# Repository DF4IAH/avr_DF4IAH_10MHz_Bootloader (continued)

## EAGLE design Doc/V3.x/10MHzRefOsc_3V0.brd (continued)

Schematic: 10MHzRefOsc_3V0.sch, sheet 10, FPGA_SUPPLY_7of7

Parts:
C1001: 100uF; C1206
C1002, C1003, C1022, C1023: 4.7uF; C0402
C1004, C1005, C1006, C1012, C1024, C1025, C1026: 0.47uF; C0402
C1011, C1021: 47uF; C0805
R101, R102, R103, R104, R105: 0; R0402
U1: XC7A35TFTG256; FTG256_0MM4

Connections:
FPGA_DXN_0: R105.1, U1.K7 (DXN_0)
FPGA_DXP_0: R104.1, U1.K8 (DXP_0)
FPGA_VCCAUX: C1021.1, C1022.1, C1023.1, C1024.1, C1025.1, C1026.1, R103.1, U1.G10 (VCCAUX), U1.J10 (VCCAUX), U1.K11 (VCCAUX), U1.L10 (VCCAUX)
FPGA_VCCBRAM: C1011.1, C1012.1, R102.1, U1.E10 (VCCBRAM), U1.F11 (VCCBRAM)
FPGA_VCCINT: C1001.1, C1002.1, C1003.1, C1004.1, C1005.1, C1006.1, R101.1, U1.F7 (VCCINT), U1.F9 (VCCINT), U1.G6 (VCCINT), U1.H9 (VCCINT), U1.J6 (VCCINT), U1.K9 (VCCINT), U1.L8 (VCCINT)
GND: C1001.2, C1002.2, C1003.2, C1004.2, C1005.2, C1006.2, C1011.2, C1012.2, C1021.2, C1022.2, C1023.2, C1024.2, C1025.2, C1026.2, R104.2, R105.2, U1.A1 (GND), U1.A11 (GND), U1.B8 (GND), U1.C5 (GND), U1.C15 (GND), U1.D2 (GND), U1.D12 (GND), U1.E9 (GND), U1.F6 (GND), U1.F10 (GND), U1.F16 (GND), U1.G3 (GND), U1.G9 (GND), U1.G13 (GND), U1.H6 (GND), U1.J9 (GND), U1.J11 (GND), U1.K4 (GND), U1.K6 (GND), U1.K14 (GND), U1.L1 (GND), U1.L11 (GND), U1.M8 (GND), U1.N5 (GND), U1.N15 (GND), U1.P2 (GND), U1.P12 (GND), U1.R9 (GND), U1.T6 (GND), U1.T16 (GND); also elsewhere on the board
PWR_1V0: R101.2, R102.2
PWR_1V8: R103.2; also elsewhere on the board

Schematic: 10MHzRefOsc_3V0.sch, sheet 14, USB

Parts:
C141: 47uF; PANASONIC_C
C142: 100n; C0805
CON141: TYCO-AMP_USBUSB-B_SMT; TYCO-AMP_USB-B_SMT
D141, D142: BZX84-C3V6; TO236
R141, R142: 68; R0805
R143: 1M; R0805
R144: 1.5k; R0805
RP141: 1206L025YR_0.5A; M1206

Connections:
GND: C141.-, C142.2, CON141.4 (GND), D141.A, D142.A, R143.1; also elsewhere on the board
USB_5V: C141.+, C142.1, RP141.2
USB_DISC: R144.2
USB_D_MIN1: CON141.2 (D-), D142.C, R142.1, R144.1
USB_D_MNS: R142.2
USB_D_PLS: R141.2
USB_D_PLS1: CON141.3 (D+), D141.C, R141.1, R143.2
USB_PWR1: CON141.1 (VBUS), RP141.1

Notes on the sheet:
USB-B

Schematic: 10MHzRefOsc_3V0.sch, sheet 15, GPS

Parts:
C151: 0.22F; PANASONIC_C
C152: 100n; C0805
CON151: HEADER-2X5SMD; 2X5SMD
D151: CRS08; SOT23
R151, R152: 10k; R0805
RP151: 1206L012WR_0.1A; M1206
U151: GLOBALTOP-FIREFLY1-GMM-G3

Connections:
GND: C151.-, C152.2, CON151.1, CON151.9, CON151.10, U151.2 (GND), U151.4 (GND), U151.8 (GND), U151.10 (GND), U151.15 (GND); also elsewhere on the board
GPS_2ND_RX: R152.1, U151.6 (RXDB)
GPS_2ND_TX: U151.5 (TXDB)
GPS_3DFIX: U151.13 (3D_FIX)
GPS_ANT: U151.1 (ANTENNA_IN); also elsewhere on the board
GPS_ANT_PWR: CON151.4, RP151.1, U151.3 (VANT)
GPS_NMEA_RX: CON151.5, U151.12 (RXDA)
GPS_NMEA_TX: CON151.6, U151.11 (TXDA)
GPS_NRESET: R151.1, U151.7 (NRESET)
GPS_PPS: CON151.7, U151.9 (1PPS)
PWR_3V3: C152.1, D151.1 (A), R151.2, R152.2, RP151.2, U151.16 (VCC_3V3); also elsewhere on the board
PWR_5V0: CON151.3
PWR_BACKUP_GPS: C151.+, CON151.2, D151.3 (C), U151.14 (VBACKUP)

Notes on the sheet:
GPS - PINs: 1 GND 2 V_BAT, Memory Supply, Goldcap 3 VCC 5V 4 V_ANT 5V, fused 5 GPS NMEA RX 6 GPS NMEA TX 7 PPS (1 Hz) 8 Ref. 10 kHz 9 GND 10 GND

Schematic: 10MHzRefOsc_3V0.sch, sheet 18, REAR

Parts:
CON181, CON183, CON184, CON185, CON186: MCX-J-P-X-RA-SM1
CON182: SD-73100-0105; MOLEX_BNC-JACK-50R_SD-73100-0105

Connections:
GND: CON181.2, CON181.3, CON181.4, CON181.5, CON182.2, CON182.3, CON183.2, CON183.3, CON183.4, CON183.5, CON184.2, CON184.3, CON184.4, CON184.5, CON185.2, CON185.3, CON185.4, CON185.5, CON186.2, CON186.3, CON186.4, CON186.5; also elsewhere on the board
GPS_ANT: CON181.1; also elsewhere on the board
REFC_10MHZ: CON182.1
SIG_CH0_I: CON183.1
SIG_CH0_Q: CON184.1
SIG_CH1_I: CON185.1
SIG_CH1_Q: CON186.1

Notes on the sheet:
10 MHz RefClk Out
GPS Ant In
CH0 I Out
CH0 Q Out
CH1 I Out
CH1 Q Out

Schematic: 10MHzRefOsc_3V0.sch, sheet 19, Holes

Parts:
H191, H192, H193, H194: MOUNT-PAD-ROUND2.8; 2,8-PAD

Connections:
GND: H191.B2,8, H192.B2,8, H193.B2,8, H194.B2,8; also elsewhere on the board

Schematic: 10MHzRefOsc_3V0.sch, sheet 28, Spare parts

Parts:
CON191: HEADER-2X3SMD; 2X03SMD
CON192: AVR-JTAG-10SMD; 2X5SMD
D191: BZX84-C2V7; TO236
L191: 10uH; L1812

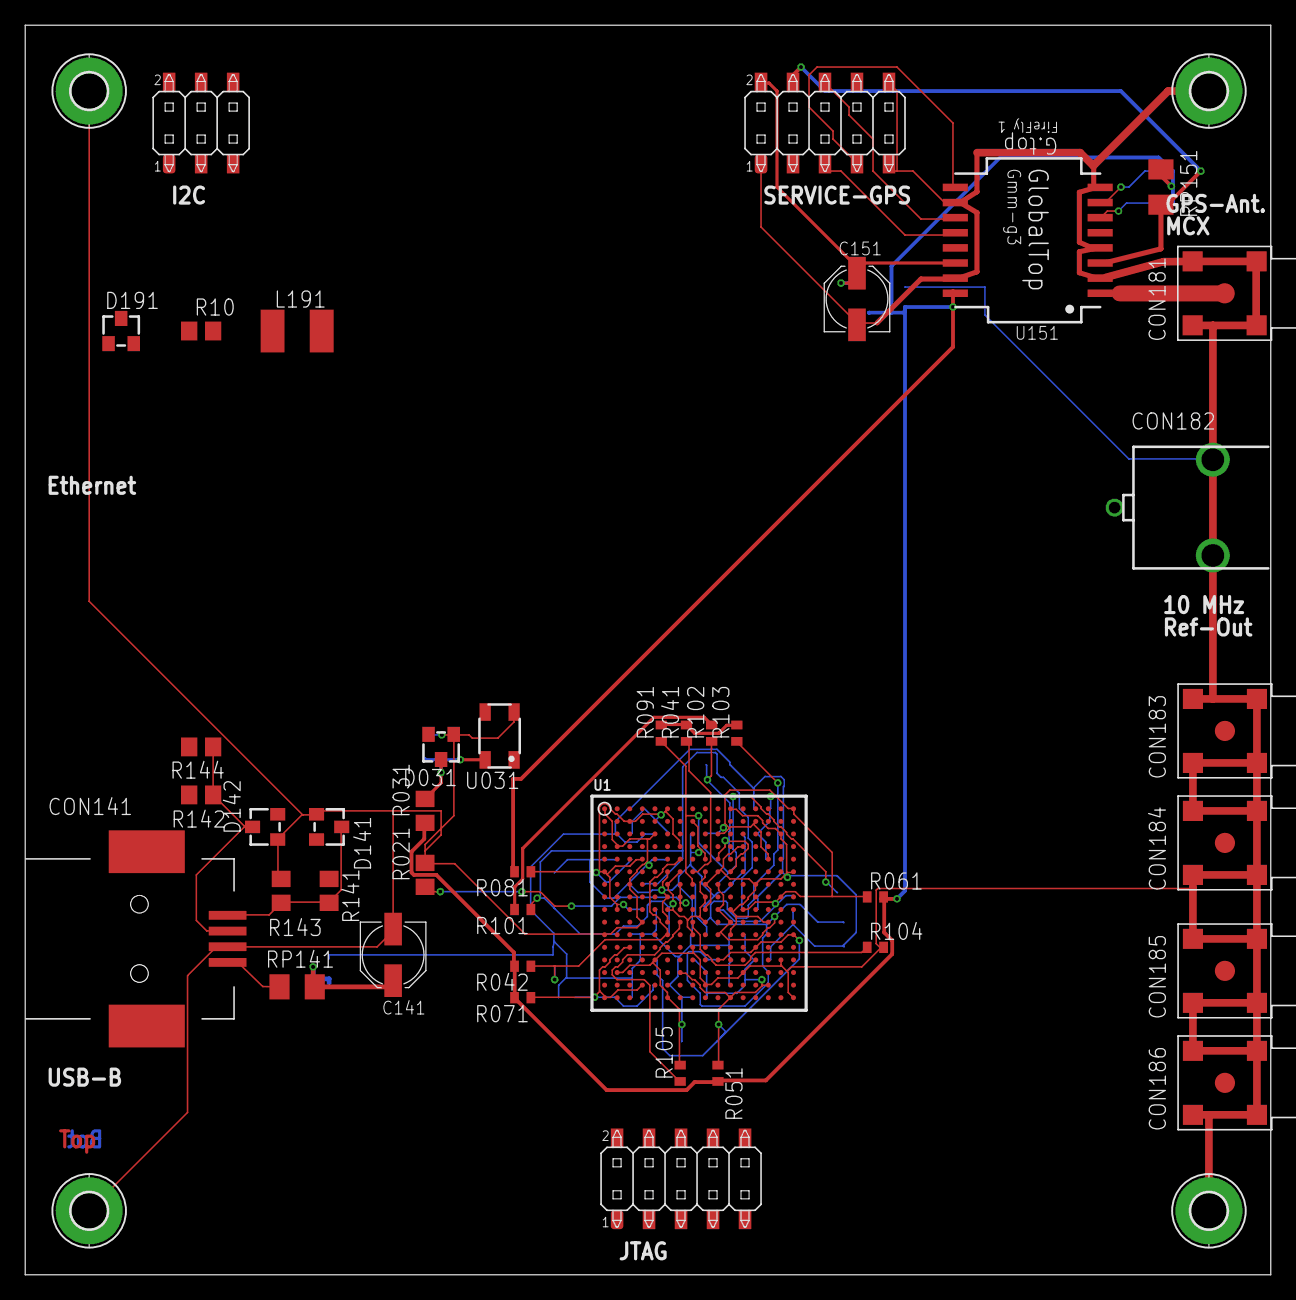
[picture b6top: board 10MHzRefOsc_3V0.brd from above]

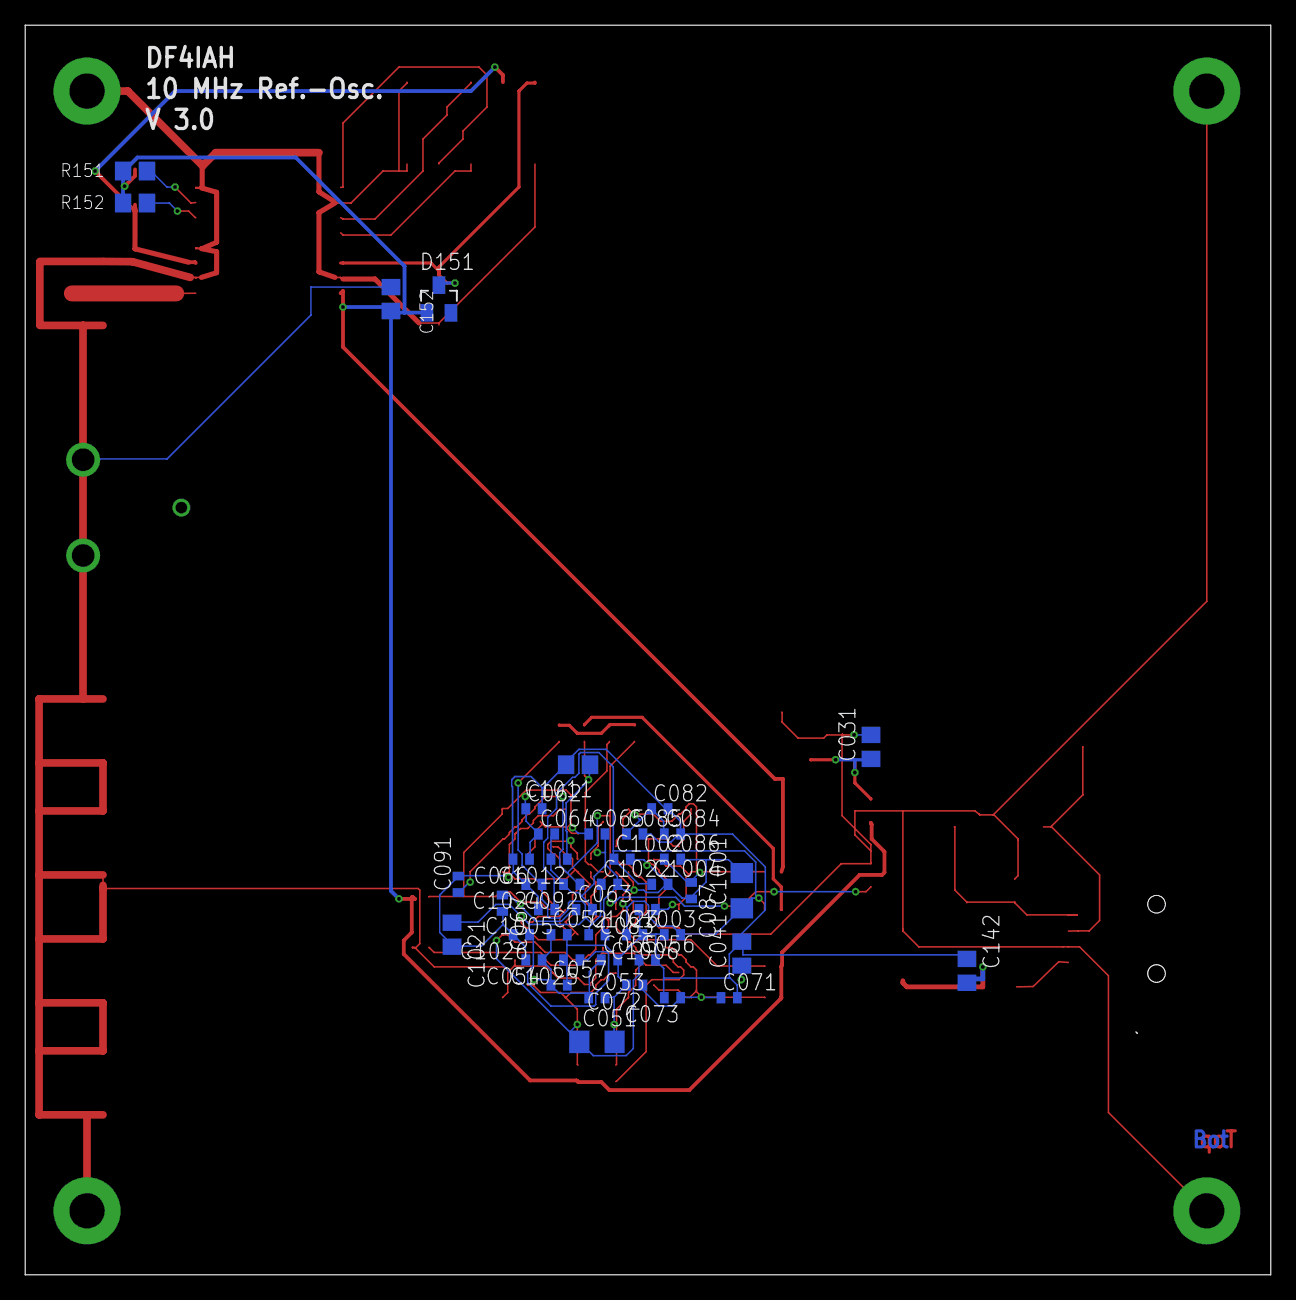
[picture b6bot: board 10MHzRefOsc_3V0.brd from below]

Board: 2 copper layers, 98.9 x 99.2 mm, 90 parts (45 on the bottom side), 30 nets.

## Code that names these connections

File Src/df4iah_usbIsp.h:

/*
 * isp.h - part of USBasp
 *
 * Autor..........: Thomas Fischl <tfischl@gmx.de>
 * Description....: Provides functions for communication/programming
 *                  over ISP interface
 * Licence........: GNU GPL v2 (see Readme.txt)
 * Creation Date..: 2005-02-23
 * Last change....: 2009-02-28
 */

#ifndef DF4IAH_USBISP_H_
#define	DF4IAH_USBISP_H_

#ifndef uchar
#define	uchar	unsigned char
#endif

#define	ISP_OUT   PORTB
#define ISP_IN    PINB
#define ISP_DDR   DDRB
#define ISP_RST   PB2
#define ISP_MOSI  PB3
#define ISP_MISO  PB4
#define ISP_SCK   PB5

/* Prepare connection to target device */
void ispConnect();

/* Close connection to target device */
void ispDisconnect();

/* read an write a byte from ISP using software (slow) */
uchar ispTransmit_sw(uchar send_byte);

/* read an write a byte from ISP using hardware (fast) */
uchar ispTransmit_hw(uchar send_byte);

/* enter programming mode */
uchar ispEnterProgrammingMode();

/* read byte from EEPROM at given address */
uchar ispReadEEPROM(unsigned int address);

/* write byte to Flash at given address */
uchar ispWriteFlash(unsigned long address, uchar data, uchar pollmode);

uchar ispFlushPage(unsigned long address, uchar pollvalue);

/* read byte from Flash at given address */
uchar ispReadFlash(unsigned long address);

/* write byte to EEPROM at given address */
uchar ispWriteEEPROM(unsigned int address, uchar data);

/* pointer to SW or HW transmit function */
uchar (*ispTransmit)(uchar);

/* set SCK speed. call before ispConnect! */
void ispSetSCKOption(uchar sckoption);

/* load extended address byte */
void ispLoadExtendedAddressByte(unsigned long address);

#endif /* DF4IAH_USBISP_H_ */

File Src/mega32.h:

#ifndef _MEGA32_H_
#define _MEGA32_H_

/* Part-Code ISP */
#define DEVTYPE_ISP     	0x72
/* Part-Code Boot */
#define DEVTYPE_BOOT    	0x73

#define SIG_BYTE1			0x1E
#define SIG_BYTE2			0x95
#define SIG_BYTE3			0x02

/* USART */
#define UART_BAUD_HIGH		UBRR0H
#define UART_BAUD_LOW		UBRR0L
#define UART_STATUS			UCSR0A
#define UART_TXREADY		UDRE0
#define UART_RXREADY		RXC0
#define UART_DOUBLE			U2X0
#define UART_CTRL			UCSR0B
#define UART_CTRL_DATA		(_BV(TXEN0 | _BV(RXEN0))	// TX enable, RX enable
#define UART_CTRL2			UCSR0C
#define UART_CTRL2_DATA		(0b11 << UCSZ00)			// 8-bit
#define UART_DATA			UDR0
#define UART_PORT			PORTD						// port D register
#define UART_DDR			DDRD						// DDR for port D
#define UART_TX_PIN			PIND						// PIN for TX pin at port D
#define UART_TX_PNUM		PIN1						// PIN number for TX pin
#define UART_RX_PIN			PIND						// PIN for RX pin at port D
#define UART_RX_PNUM		PIN0						// PIN number for RX pin

/* Timer-n compare output */
#define DDR_OC0A_REG		DDRD
#define DDR_OC0A			PD6
#define DDR_OC0B_REG		DDRD
#define DDR_OC0B			PD5
#define DDR_OC1A_REG		DDRB
#define DDR_OC1A			PB1
#define DDR_OC1B_REG		DDRB
#define DDR_OC1B			PB2
#define DDR_OC2A_REG		DDRB
#define DDR_OC2A			PB3
#define DDR_OC2B_REG		DDRD
#define DDR_OC2B			PD3

/*
 * Pin "STARTPIN" on port "STARTPORT" in this port has to grounded
 * (active low) to start the bootloader
 */
#define PROBE_DDR			DDRD
#define PROBE_PORT			PORTD
#define PROBE_PIN			PIND
#define PROBE_PNUM			PIN3						// JP3 BootLoader

/* Debugging toggle pin */
#define PWMTOGGLEPIN_DDR	DDRC
#define PWMTOGGLEPIN_PORT	PORTC
#define PWMTOGGLEPIN_PIN	PINC
#define PWMTOGGLEPIN_PNUM	PIN5						// PC5(ADC5/SCL) - Pin 28

/* BOOT token and place of BOOT token as offset before RAMEND */
# define BOOT_TOKEN			0xb00f
# define BOOT_TOKEN_EE_ADR	0x3fa						// @see df4iah_fw_memory.h

#endif // #ifndef _MEGA32_H_

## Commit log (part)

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2014-10-25 avr_DF4IAH_Bootloader - copy from avr_Bootloader_0v85
2014-10-25 avr_DF4IAH_Bootloader - first compilation
2014-10-25 avr_DF4IAH_Bootloader - Src subdirectory established
2014-10-30 avr_DF4IAH_Bootloader - changed bootsize to 2k-words, starting @ 0x7000
2014-11-01 avr_DF4IAH_Bootloader - compatibility with AVR109 established, compared with Bootloader of HF-Messzwerg
2014-11-02 avr_DF4IAH_Bootloader - some more refactoring
2014-11-02 avr_DF4IAH_Bootloader - some more tweaks done for usbdrv setup
2014-11-02 avr_DF4IAH_Bootloader - code placement added
2014-11-02 avr_DF4IAH_Bootloader - between serial and usb can now be selected
2014-11-24 avr_DF4IAH_Bootloader - between serial and usb can now be selected (2)
2014-11-27 avr_DF4IAH_Bootloader - PWM output to pull crystal added (2)
2014-11-27 avr_DF4IAH_Bootloader - fire-up the first time (2)
2014-11-27 avr_DF4IAH_Bootloader - fire-up the first time (3)
2014-11-27 avr_DF4IAH_Bootloader - wireDebug disabled
2014-11-27 avr_DF4IAH_Bootloader - BrownOutDetection=2.7V, DebugWire=on, ISP=on
2014-11-27 avr_DF4IAH_Bootloader - moved debug_endlessTogglePin() before init_usb()
2014-11-27 avr_DF4IAH_Bootloader - USB_CFG_HAVE_MEASURE_FRAME_LENGTH disabled
2014-11-28 avr_DF4IAH_Bootloader - USB device description changed to USBasp (2)
2014-11-28 avr_DF4IAH_Bootloader - USBasp firmware included
2014-11-28 avr_DF4IAH_Bootloader - USBasp stack joined with avrboot code
2014-11-29 avr_DF4IAH_Bootloader - with this configuration USB works :-)
2014-11-29 avr_DF4IAH_Bootloader - with this configuration USB still works :-)
2014-11-30 avr_DF4IAH_Bootloader - wrong assumptions corrected, we do not use the Tiny Programming Interface (TPI)
2014-11-30 avr_DF4IAH_Bootloader - Release added to the ignore list
2014-11-30 avr_DF4IAH_Bootloader - mimic signature - bad response
2014-11-30 avr_DF4IAH_Bootloader - EEPROM and Flash, READ and WRITE now OK :-)
2014-11-30 avr_DF4IAH_Bootloader - enhancing Flash WRITE to automagically erasing pages during write operation
2014-11-30 avr_DF4IAH_Bootloader - new memory layout
2014-11-30 avr_DF4IAH_Bootloader - USB poll interval increased to 25 ms
2014-12-01 avr_DF4IAH_Bootloader - SPI does only work when DebugWire is turned off
2014-12-03 avr_DF4IAH_Bootloader - writeFlashPage rewritten
2014-12-03 avr_DF4IAH_Bootloader - writeFlashPage() is OK now
2014-12-03 avr_DF4IAH_Bootloader - writeFlashPage() is OK now (2)
2014-12-04 avr_DF4IAH_Bootloader - renaming done to distinguish between BL (bootloader) and FW (code) (2)
2014-12-04 avr_DF4IAH_Bootloader - bootloader and firmware distinguished
2014-12-04 avr_DF4IAH_Bootloader - bootloader and firmware distinguished (2)
2014-12-04 avr_DF4IAH_Bootloader - bad APP_END behavior in memory_bl_writeFlashPage corrected
2014-12-06 avr_DF4IAH_Bootloader - programming fuses added
2014-12-13 avr_DF4IAH_Bootloader - usbFunctionSetup() cleaned up
2014-12-24 avr_DF4IAH_Bootloader - try new swap bootloader and memory layout
2014-12-24 avr_DF4IAH_Bootloader - sample TOKEN bytes at the start-up
2014-12-24 avr_DF4IAH_Bootloader - jump to FW and BL now OK
2014-12-24 avr_DF4IAH_Bootloader - jump to FW and BL now OK (3)
2014-12-25 avr_DF4IAH_Bootloader - USB bug removed
2014-12-26 avr_DF4IAH_Bootloader - switch off modules that are not needed, USB power: 210 mA
2014-12-27 avr_DF4IAH_Bootloader - new default PWM value 0xC000
2014-12-28 avr_DF4IAH_Bootloader - version string updated
2014-12-28 avr_DF4IAH_Bootloader - redefinition of BOOT_TOKEN removed
2014-12-29 avr_DF4IAH_Bootloader - address of BOOT_TOKEN changed
2014-12-29 avr_DF4IAH_Bootloader - DEFAULT_PWM_COUNT changed to 0xB800
2014-12-29 avr_DF4IAH_Bootloader - toggle PIN not masked correctly (2)
2014-12-29 avr_DF4IAH_Bootloader - volatile reduced
2014-12-30 avr_DF4IAH_Bootloader - Hardware V1.1 --> V1.2
2014-12-31 avr_DF4IAH_Bootloader - new default startup PWM value
2014-12-31 avr_DF4IAH_Bootloader - startup PWM value up-heated oscillator
2015-01-01 avr_DF4IAH_Bootloader - startup PWM value up-heated oscillator (2)
2015-01-15 avr_DF4IAH_Bootloader - CPLD - moved here
2015-01-15 avr_DF4IAH_Bootloader - CPLD - VHDL TestBench added - TODO: functional and timing simulations
2015-01-15 avr_DF4IAH_Bootloader - Doc - Eagle: last updates of the circuit added (V2.0)
2015-01-16 avr_DF4IAH_Bootloader - CPLD - serial communication paths added
2015-01-18 avr_DF4IAH_Bootloader - Doc - Eagle: USB-B and BNC connectors changed
2015-01-18 avr_DF4IAH_Bootloader - Doc - Eagle: ISP-Connector changed from old 10 to new 6 pin variant
2015-01-20 avr_DF4IAH_Bootloader - Doc - Eagle: V2.0.1 manufactured by PCB-Pool - corrections needed
2015-01-26 avr_DF4IAH_Bootloader - Doc - Eagle: setting-up V3.0
2015-01-26 avr_DF4IAH_Bootloader - Doc - Eagle: V3.0 - REAR panel connected
2015-01-27 avr_DF4IAH_Bootloader - Doc - Eagle: current df4iah.lbr added
2015-01-27 avr_DF4IAH_Bootloader - Doc - Eagle: V2.1 after manufacturing by PCB-Pool - findings to be fixed (2) - BNC-Drills size doubled, Goldcap bigger than assumed, switching converter had wrong PIN assignme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
2015-01-28 avr_DF4IAH_Bootloader - Doc - Eagle: V3.0 - FPGA and MMU, first attempt, added
2015-02-01 avr_DF4IAH_Bootloader - Doc - Eagle: df4iah.lbr - LINX RXM-GNSS-TM chip entries corrected
2015-02-01 avr_DF4IAH_Bootloader - Doc - Eagle: V2.1 after manufacturing by PCB-Pool - findings to be fixed (4) - change R81 from 1k to 150Ohm, 3.3V regulator corrected.
2015-02-04 avr_DF4IAH_Bootloader - Doc - Eagle: V3.0 - MMU (AVR ATmega) moved into FPGA using a free MMU core from opencores.org.
2015-02-04 avr_DF4IAH_Bootloader - Doc - Eagle: V3.0 - xilinx_devices_V6.lbr containing XC7-Artix added (2)
2015-02-05 avr_DF4IAH_Bootloader - Doc - Eagle: structuring into V1.x, V2.x and V3.x (1)
2015-02-05 avr_DF4IAH_Bootloader - Doc - Eagle: structuring into V1.x, V2.x and V3.x (3)
2015-02-05 avr_DF4IAH_Bootloader - CPLD - multiple changes, now CPLD works as intended
2015-02-07 avr_DF4IAH_Bootloader - Doc - Eagle: main df4iah.lbr library split into sub-libraries
2015-02-07 avr_DF4IAH_Bootloader - Doc - Eagle: V2.1 - OP-Amps U4 and U5 added/changed
2015-02-15 avr_DF4IAH_Bootloader - Doc - Eagle: V2.1 - Sample&Hold - reduce from 10nF to 100pF, components are renamed (2)
2015-02-15 avr_DF4IAH_Bootloader - CPLD - V2.1 uses GPS PPS-signal only, switch from 10kHz to 1Hz
2015-02-16 avr_DF4IAH_Bootloader - CPLD - V2.1 uses CPLD to drive the PWM_PULL RC-network due to the regulated 3.3V source of the CPLD. The AVR is at 5.0V unregulated USB-Bus that resulted in non-accurate pull 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
2015-02-17 avr_DF4IAH_Bootloader - Doc - Compilation-SizeCompare - added. Win7 results are outdated.
2015-02-17 avr_DF4IAH_Bootloader - Doc - Copilation-SizeCompare - Bootloader/Ubuntu added
2015-02-17 avr_DF4IAH_Bootloader - Doc - Compilation-SizeCompare - MAC Bootloader/Firmware updated
2015-02-19 avr_DF4IAH_Bootloader - default PWM value modified
2015-02-19 avr_DF4IAH_Bootloader - Doc - Eagle: V2.1 - R411 modified, CPLD pinout changed
2015-02-24 avr_DF4IAH_Bootloader - Src - df4iah_bl_clkPullPwm module now without clkPullPwm_bl_setRatio(), DEFAULT_PWM_COUNT changed from 155 to 90.
2015-02-25 avr_DF4IAH_Bootloader - Src - avrdude programming e-fuse: keep D.C.s at '1'
2015-02-25 avr_DF4IAH_Bootloader - Revert most changes on mega32.h. Moved extras to df4iah_bl_main.h
2015-03-01 avr_DF4IAH_Bootloader - Src - avr-size switched from Berkeley to SYSV format. Using UTF-8 for all files now.
2015-03-01 avr_DF4IAH_Bootloader - Doc - Eagle: V2.1 - PWM pull signal via CPLD for clamping signals to defined values. AVR controller @ USB is not voltage regulated, the PWM output is therefore variable in its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
2015-03-12 avr_DF4IAH_Bootloader - CPLD - 10 MHz out signal negated to have that signal in phase with the 1PPS signal
2015-03-17 avr_DF4IAH_Bootloader - Doc - Eagle: V2.1 - with GPS module Linx - sent to DirtyPCBs
2015-03-17 avr_DF4IAH_Bootloader - Doc - Eagle: V2.2 - with GPS module GlobalTop - sent to DirtyPCBs
2015-03-26 avr_DF4IAH_Bootloader - Doc - Eagle: V2.2 - correction: CRS80 --> CRS08
2015-03-26 avr_DF4IAH_Bootloader - Doc - Eagle: V2.1 - correction: CRS80 --> CRS08 (2)
2015-03-26 avr_DF4IAH_Bootloader - Doc - Eagle: V2.x - *.pro files removed
2015-03-30 avr_DF4IAH_Bootloader - Doc - Eagle: V2.1/V2.2 - removed elkos and replaced it by C0805 MLCCs
2015-04-09 avr_DF4IAH_Bootloader - CPLD - simple PWM transfer added: 5V in, 3.3V out
2015-04-12 avr_DF4IAH_Bootloader - Doc - Eagle: V2.3 - added. Contains GPS-module TJ1513MTBD which is based on the MediaTek MT3333 chip-set (2)
2015-04-20 avr_DF4IAH_Bootloader - Doc - Eagle: 2.x - 10 MHz signal spectrum
2015-04-20 avr_DF4IAH_Bootloader - Doc - Versandtaschen added (2)
2015-04-20 avr_DF4IAH_Bootloader - Doc - Eagle: 2.1, 2.2, 2.3 - three resistors changed
2015-04-23 avr_DF4IAH_Bootloader - Doc - Versandtasche for LCD-Module updated
2015-04-24 avr_DF4IAH_Bootloader - Doc - naming of 10MHz-Ref-Osc corrected (1)
2015-04-24 avr_DF4IAH_Bootloader - Doc - Versandtasche for 10MHzRefOsc updated
2015-04-24 avr_DF4IAH_Bootloader - Doc - Versandtasche for 10MHzRefOsc updated - R311 correction (2)
2015-04-25 avr_DF4IAH_Bootloader - CPLD - variant: 1 MHz instead of 10 MHz output
2015-04-25 avr_DF4IAH_Bootloader - Doc - Versandtasche for 10MHzRefOsc updated - CPLD: current RTL images included
2015-04-25 avr_DF4IAH_Bootloader - CPLD - now 10 MHz (default) or 1 MHz (low @ 10 kHz input line) at BNC (Pin 40)
2015-04-25 avr_DF4IAH_Bootloader - Doc - Versandtasche for 10MHzRefOsc updated - CPLD: 10/1 MHz select, RTL pictures updated
2015-04-25 avr_DF4IAH_Bootloader - Doc - Versandtasche for 10MHzRefOsc updated - CPLD: 10/1 MHz select, RTL pictures updated (2)
2015-04-29 avr_DF4IAH_Bootloader - CPLD - 2.5 MHz sync'ing 0° and 180° to be ready in less time
2015-04-29 avr_DF4IAH_Bootloader - CPLD - invertion of 10 MHz removed
2015-05-08 avr_DF4IAH_Bootloader - Doc - Eagle: 2.2 - 3.3V adjusting resistors corrected
2015-05-11 avr_DF4IAH_Bootloader - Doc - ISP - ISP__avr_DF4IAH_Bootloader.hex 20150312 added
2015-05-11 avr_DF4IAH_Bootloader - Doc - ISP - ISP__avr_DF4IAH_10MHz_Reference.hex, ISP__avr_DF4IAH_10MHz_Reference.eep 20150429 added
2015-05-11 avr_DF4IAH_Bootloader - Doc - ISP - ISP programming scripts added (2)
2015-05-11 avr_DF4IAH_Bootloader - CPLD - df4iah_10mhz_ref_osc_v2.lct removed
2015-05-11 avr_DF4IAH_Bootloader - CPLD - df4iah_10mhz_ref_osc_v2.svf updated (2)
2015-05-12 avr_DF4IAH_Bootloader - CPLD - df4iah_10mhz_ref_osc_v2.svf updated (4)
2016-09-07 avr_DF4IAH_Bootloader - README.md - first update
2016-09-07 avr_DF4IAH_Bootloader - README.md - missings added
2016-09-07 avr_DF4IAH_Bootloader - README.md - author
2016-09-07 avr_DF4IAH_Bootloader - README.md - additionals
2016-09-07 avr_DF4IAH_Bootloader - README.md - Credits
2016-09-07 avr_DF4IAH_10MHz_Reference - README.md - contents
2017-01-03 avr_DF4IAH_Bootloader - Images folder added
2017-01-03 avr_DF4IAH_Bootloader - script added to program the ATmega-328P Fuses and the Bootloader
2017-01-30 Doc - V2.3 - dimension rulers added: 90mm x 70mm
2017-03-11 Doc - V2.3e - via 0.6mm --> 0.35mm
2017-03-19 SW_V2.x.1 - some more tweaks done
2017-03-20 SW_V2.x.1 - Info about Bootloader added
2017-03-20 HW_V2.1.1 - new branch
2017-03-20 HW_V2.3.1 - new branch
2017-03-20 LCD_V2.x.1 - dropping unneeded things
2017-03-20 HW_V2.3.1 - dropping unneeded things
2017-03-20 HW_V2.1.1 - dropping unneeded things
2017-03-20 master - SW_V2.x.1 merged
2017-03-20 HW_V2.1.1 - .gitignore modified
2017-03-20 HW_V2.3.1 - .gitignore modified
2017-03-23 HW_V2.2 - remove V2.1 und V2.3 Eagle files, only
2017-03-23 HW_V2.3 - remove V2.1 und V2.2 Eagle files, only
2017-03-23 HW_V2.2 - remove V2.1 und V2.3 Eagle files, only - again
2017-03-23 SW_V2.x - missing binaries added
2017-04-10 SW - programmer script expanded
2017-04-10 SW - check for a valid flash image in app section relaxed
2017-04-11 HW_V2.1.1 - CPLD - new phase compare frequency of 250kHz instead of 2.5MHz
2017-04-11 HW_V2.2.1 - CPLD - new phase compare frequency of 250kHz instead of 2.5MHz
2017-06-15 SW - Script for programming the ATmega328P fixed
2017-08-23 MIT LICENSE file added
2017-12-01 Programmer script - missing execution flags added
2018-07-05 HW_V2.2.1 - GPS connector - fixed 5V to 3V3 in info block
